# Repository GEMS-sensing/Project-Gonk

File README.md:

# Project-Gonk
Hardware files for battery holder systems with integrated protection 

## Notation
#### Example: 18650 1S3P 

18650 -> Model of battery used <br>
1S -> The number of cells in <b>series</b><br>
3P -> The number of cells in <b>parallel</b><br>

Output Voltage = SeriesNumber * CellVoltage<br>
Capacity = ParallelNumber * CellCapacity<br>

## Models
- [18650 1S3P](18650_1S3P)

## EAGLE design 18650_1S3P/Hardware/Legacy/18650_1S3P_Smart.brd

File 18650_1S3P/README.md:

# Project-Gonk 
### Battery: 18650 
### Configuration: 1S3P
Battery holder with integrated protection and control

# Usage
1. Toggle switch to "<b>OFF</b>" position
2. Verify battery voltage (Maximum difference between highest and lowest voltage cell should be less than <b>0.2V</b>)
3. Insert batteries into holders (<b>Note polarity markings</b>)
4. Verify polarity - if any of the <b>red indicator lamps</b> are lit, <b>stop!</b> Remove offending batteries and fix polarity before proceeding
5. If no red lamps are lit, connect external system to either of the <b>Vout</b> connectors (<b>observe polarity of connector!</b>)
6. Toggle switch to "<b>ON</b>" position when ready to activate 

# Repo Roadmap
#### [Documents](Documents/) 

General document and image storage for repo and README

#### [Hardware](Hardware/)

Current board files (Eagle), Bill of Materials (BoM), and other design documents

#### [Production](Production/)

Contains the various Gerber and pick and place files required to have the Printed Circuit Boards (PCBs) manufactured or populated 

## Overview
* **Type:** Power
* **Interfaces:** Power
* **Release Version:** v0.1

<!--  -->

<!--  -->

## Features
### On-Board
* Power switch
* Reverse battery indication
* Poly fuse per battery

### Interface

## Specifications
* **Output Current (Max Constant):** 5.25A
* **Current Per Battery (Max Constant):** 1.75A

## Jumper Settings 

**Configuration Jumpers**
| Jumper | Purpose | Open | Closed | Default | 
| ------ | ------- | ---------- | ---------- | ----- | 
| `JP1` | Bypass poly fuse on battery 1 | Short Circuit Protection Enabled | Short Circuit Protection Disabled | Open |  
| `JP2` | Bypass poly fuse on battery 2 | Short Circuit Protection Enabled | Short Circuit Protection Disabled | Open |
| `JP3` | Bypass poly fuse on battery 3 | Short Circuit Protection Enabled | Short Circuit Protection Disabled | Open | 

## Known Issues/Errata

#### None!

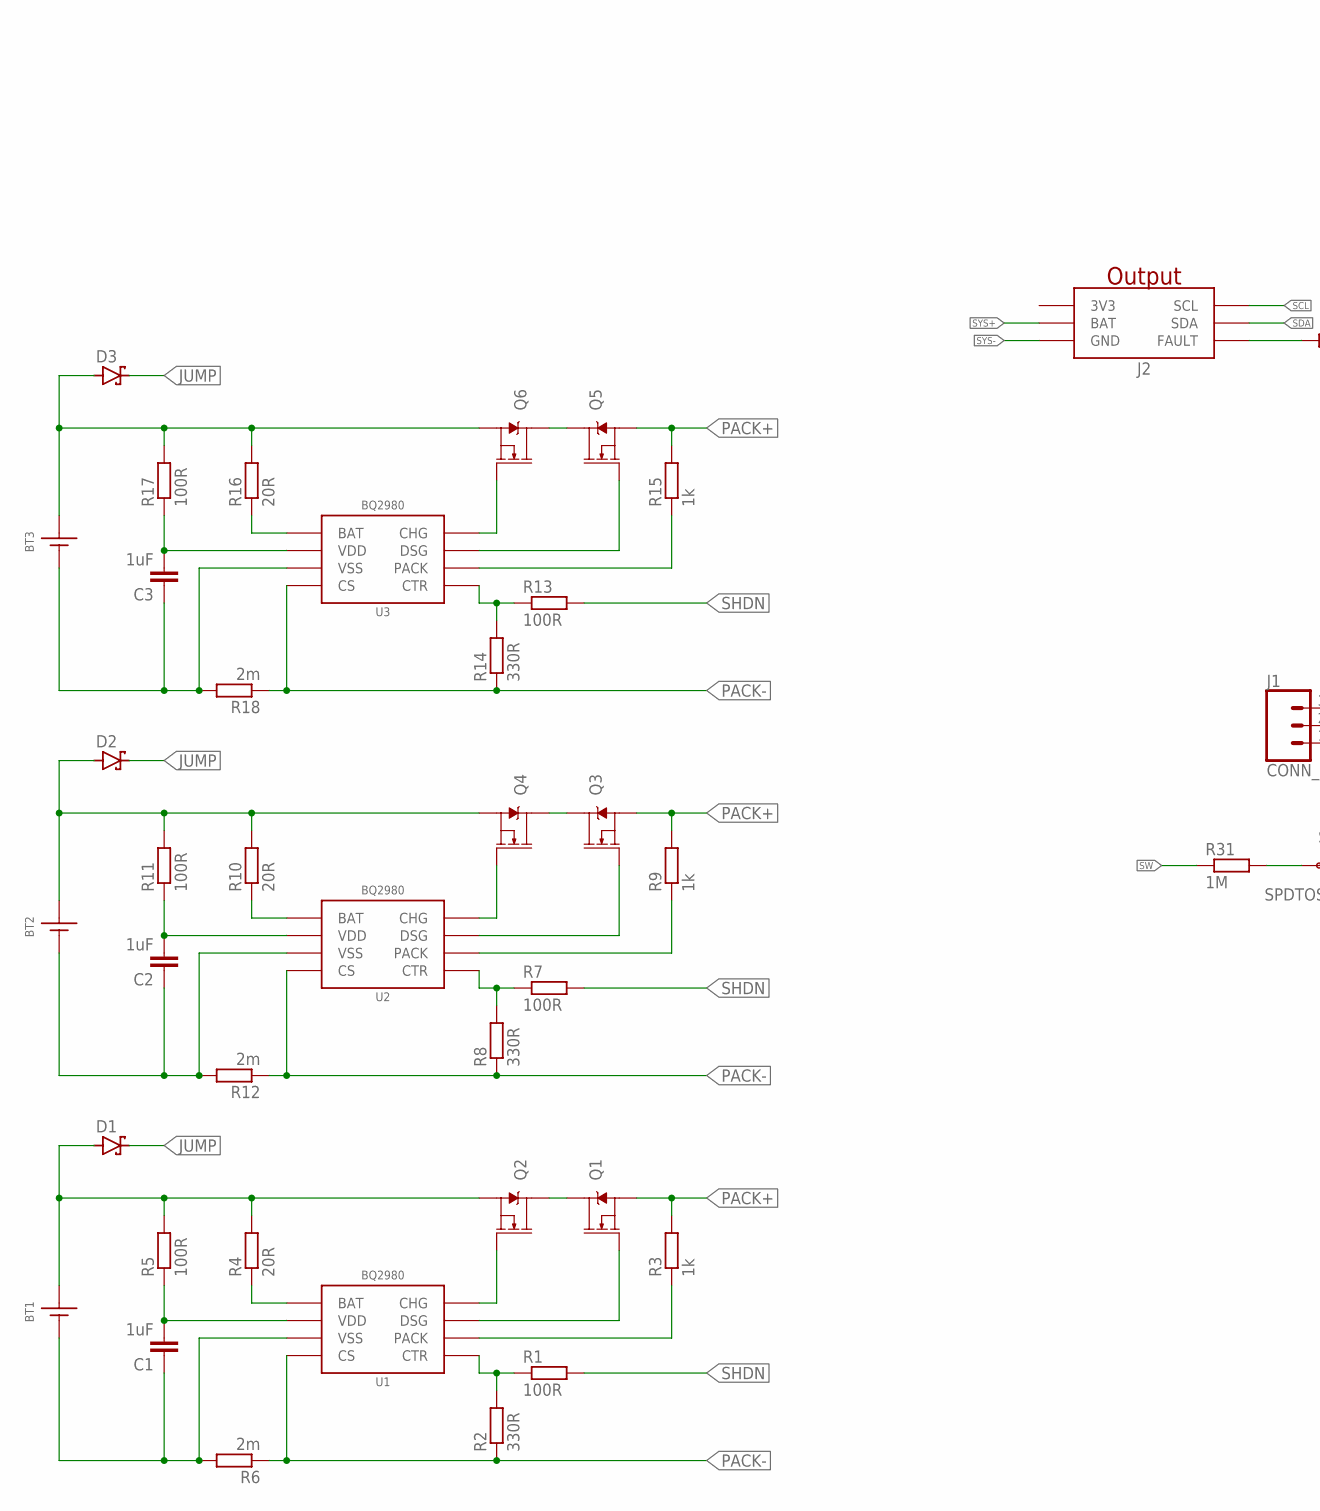
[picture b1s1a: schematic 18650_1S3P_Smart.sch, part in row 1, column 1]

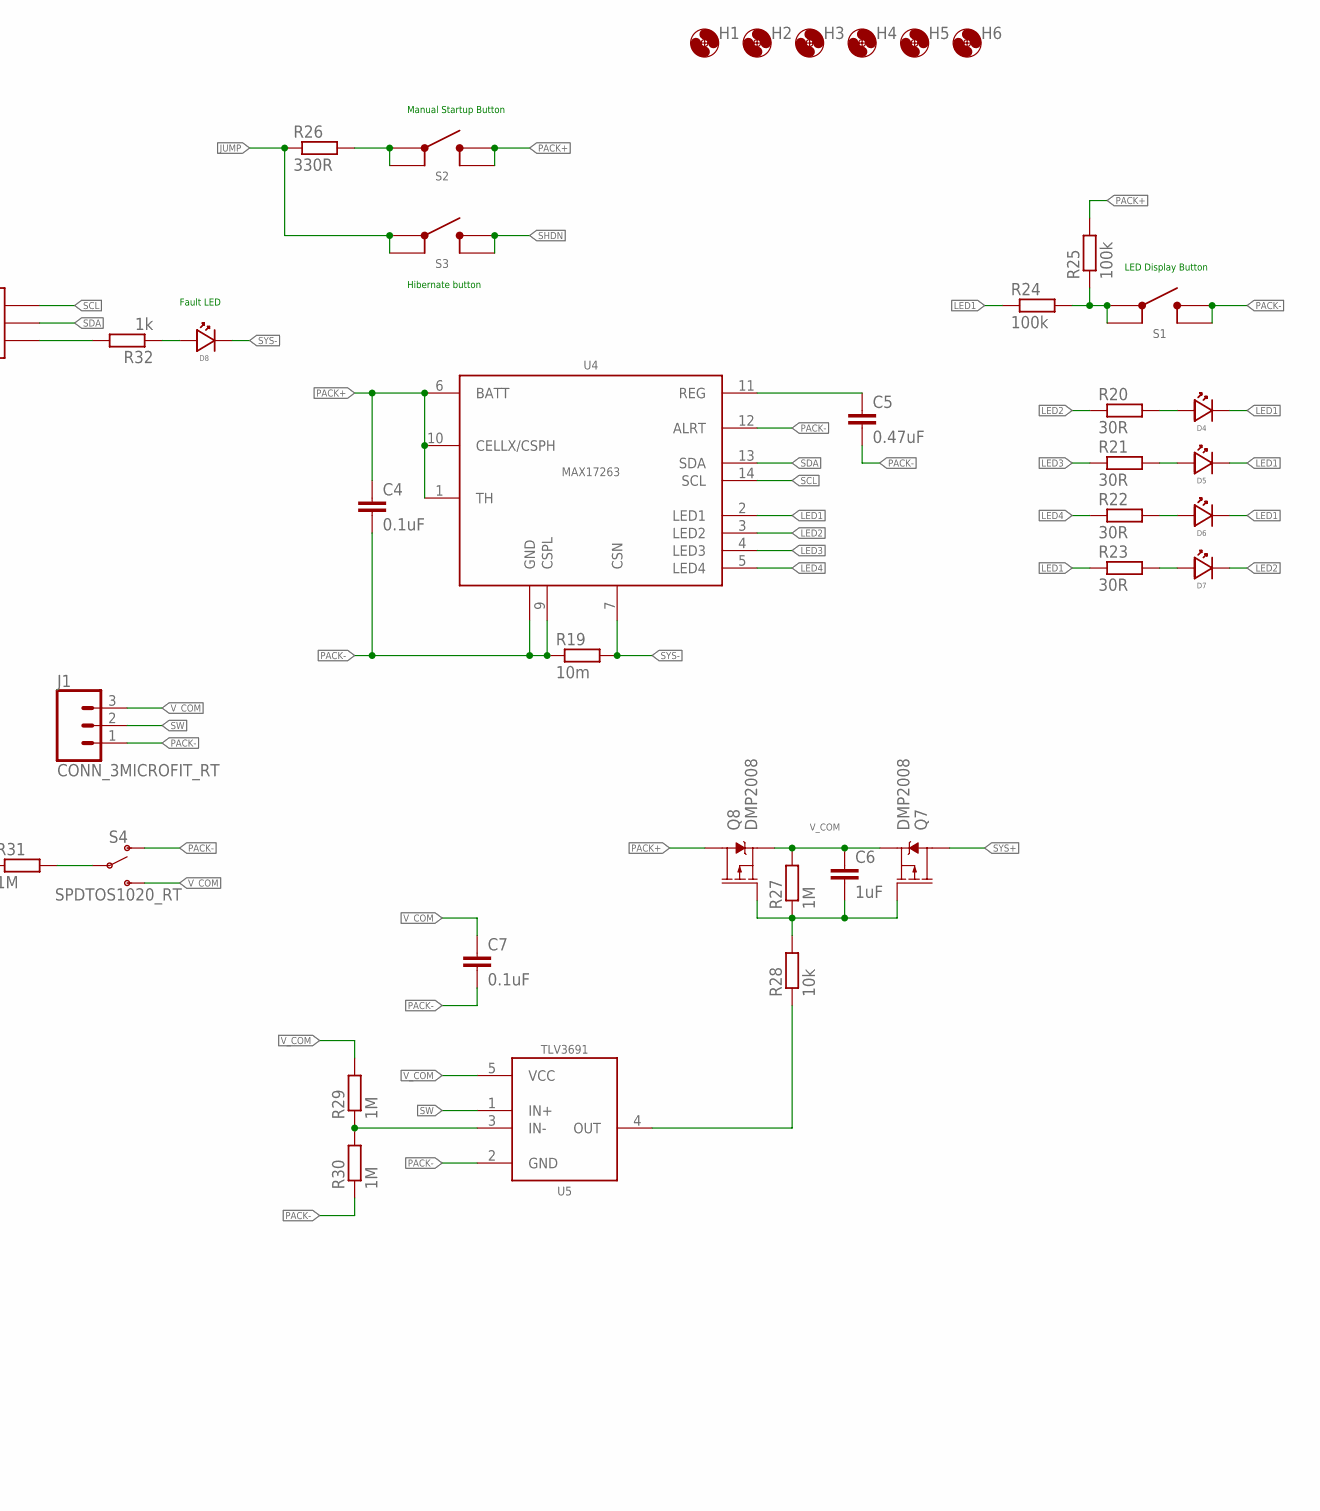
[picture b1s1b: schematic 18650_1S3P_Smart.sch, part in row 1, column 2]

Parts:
BT1, BT2, BT3: 186501042P_NOSILK; BATT_1042P_NOSILK
C1, C2, C3, C6: 1uF; C0603
C4, C7: 0.1uF; C0603
C5: 0.47uF; C0603
D1, D2, D3: DIODE_SCHOTTKYSOD-323; SOD323-R; MPN BAT54WS-7-F; DIGIKEY BAT54WS-FDICT-ND
D4, D5, D6, D7: LED1206_BOTTOM; LED_1206_BOTTOM; MPN LTST-C230KGKT; DIGIKEY 160-1456-1-ND
D8: LED1206_BOTTOM; LED_1206_BOTTOM; MPN LTST-C230KRKT; DIGIKEY 160-1457-1-ND
H1, H2, H3, H4, H5, H6: MOUNTING_HOLE4_NP; 4_40
J1: CONN_3MICROFIT_RT; 1X3_MICROFIT_RT
J2: GEMS_POWER_PLUGOUTPUT; 2X3_MICROFIT_RT
Q1, Q2, Q3, Q4, Q5, Q6: AON7522E; DFN3X3A_8L_EP1_P
Q7, Q8: DMP2008; POWERDI3333-8
R1, R5, R7, R11, R13, R17: 100R; R0603
R2, R8, R14, R26: 330R; R0603
R3, R9, R15, R32: 1k; R0603
R4, R10, R16: 20R; R0603
R6, R12, R18: 2m; R0805
R19: 10m; R0805
R20, R21, R22, R23: 30R; R0603
R24, R25: 100k; R0603
R27, R29, R30, R31: 1M; R0603
R28: 10k; R0603
S1, S2, S3: BUTTON6X6_TH; SWITCH_6MM_TH
S4: SPDTOS1020_RT; OS102011MA1QN1
U1, U2, U3: BQ2980RUG; RUG_S-PQFP-N8
U4: MAX17263; DFN_14_3X3
U5: TLV3691DCK; DCK_R-PDSO-G5

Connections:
3V3: J2.5 (3V3)
JUMP: D1.C, D2.C, D3.C, R26.1, S3.1, S3.2
LED1: D4.CATHODE, D5.CATHODE, D6.CATHODE, R23.1, R24.1, U4.2 (LED1)
LED2: D7.CATHODE, R20.1, U4.3 (LED2)
LED3: R21.1, U4.4 (LED3)
LED4: R22.1, U4.5 (LED4)
unnamed: Q1.D, Q2.D
unnamed: Q2.G, U1.8 (CHG)
unnamed: Q1.G, U1.7 (DSG)
unnamed: R1.1, R2.2, U1.5 (CTR)
unnamed: R3.1, U1.6 (PACK)
unnamed: BT1.BATT+ (+), D1.A, Q2.S@1 (S), Q2.S@2 (S), Q2.S@3 (S), R4.2, R5.2
unnamed: C1.2, R5.1, U1.2 (VDD)
unnamed: R4.1, U1.1 (BAT)
unnamed: BT1.BATT- (-), C1.1, R6.2, U1.3 (VSS)
unnamed: Q3.D, Q4.D
unnamed: Q4.G, U2.8 (CHG)
unnamed: Q3.G, U2.7 (DSG)
unnamed: R9.1, U2.6 (PACK)
unnamed: R7.1, R8.2, U2.5 (CTR)
unnamed: BT2.BATT+ (+), D2.A, Q4.S@1 (S), Q4.S@2 (S), Q4.S@3 (S), R10.2, R11.2
unnamed: C2.2, R11.1, U2.2 (VDD)
unnamed: R10.1, U2.1 (BAT)
unnamed: BT2.BATT- (-), C2.1, R12.2, U2.3 (VSS)
unnamed: Q5.D, Q6.D
unnamed: Q6.G, U3.8 (CHG)
unnamed: Q5.G, U3.7 (DSG)
unnamed: R15.1, U3.6 (PACK)
unnamed: R13.1, R14.2, U3.5 (CTR)
unnamed: BT3.BATT+ (+), D3.A, Q6.S@1 (S), Q6.S@2 (S), Q6.S@3 (S), R16.2, R17.2
unnamed: C3.2, R17.1, U3.2 (VDD)
unnamed: R16.1, U3.1 (BAT)
unnamed: BT3.BATT- (-), C3.1, R18.2, U3.3 (VSS)
unnamed: D4.ANODE, R20.2
unnamed: D5.ANODE, R21.2
unnamed: D6.ANODE, R22.2
unnamed: D7.ANODE, R23.2
unnamed: R24.2, R25.1, S1.1, S1.2
unnamed: C5.1, U4.11 (REG)
unnamed: R26.2, S2.1, S2.2
unnamed: R31.2, S4.2
unnamed: C6.2, Q7.4 (G), Q8.4 (G), R27.1, R28.2
unnamed: R28.1, U5.4 (OUT)
unnamed: J2.1 (FAULT), R32.2
unnamed: R29.1, R30.2, U5.3 (IN-)
unnamed: D8.ANODE, R32.1
PACK+: C4.1, Q1.S@1 (S), Q1.S@2 (S), Q1.S@3 (S), Q3.S@1 (S), Q3.S@2 (S), Q3.S@3 (S), Q5.S@1 (S), Q5.S@2 (S), Q5.S@3 (S), Q8.EP@1 (D), Q8.EP@2 (D), Q8.EP@3 (D), Q8.EP@4 (D), Q8.EP@5 (D), R3.2, R9.2, R15.2, R25.2, S2.3, S2.4, U4.1 (TH), U4.6 (BATT), U4.10 (CELLX/CSPH)
PACK-: C4.2, C5.2, C7.2, J1.1, R2.1, R6.1, R8.1, R12.1, R14.1, R18.1, R19.1, R30.1, S1.3, S1.4, S4.1 (O), U1.4 (CS), U2.4 (CS), U3.4 (CS), U4.8 (GND), U4.9 (CSPL), U4.12 (ALRT), U4.EP (GND), U5.2 (GND)
SCL: J2.4 (SCL), U4.14 (SCL)
SDA: J2.6 (SDA), U4.13 (SDA)
SHDN: R1.2, R7.2, R13.2, S3.3, S3.4
SW: J1.2, R31.1, U5.1 (IN+)
SYS+: J2.3 (BAT), Q7.EP@1 (D), Q7.EP@2 (D), Q7.EP@3 (D), Q7.EP@4 (D), Q7.EP@5 (D)
SYS-: D8.CATHODE, J2.2 (GND), R19.2, U4.7 (CSN)
V_COM: C6.1, C7.1, J1.3, Q7.1 (S), Q7.2 (S), Q7.3 (S), Q8.1 (S), Q8.2 (S), Q8.3 (S), R27.2, R29.2, S4.3 (S), U5.5 (VCC)

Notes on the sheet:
LED Display Button
Manual Startup Button
Hibernate button
Fault LED

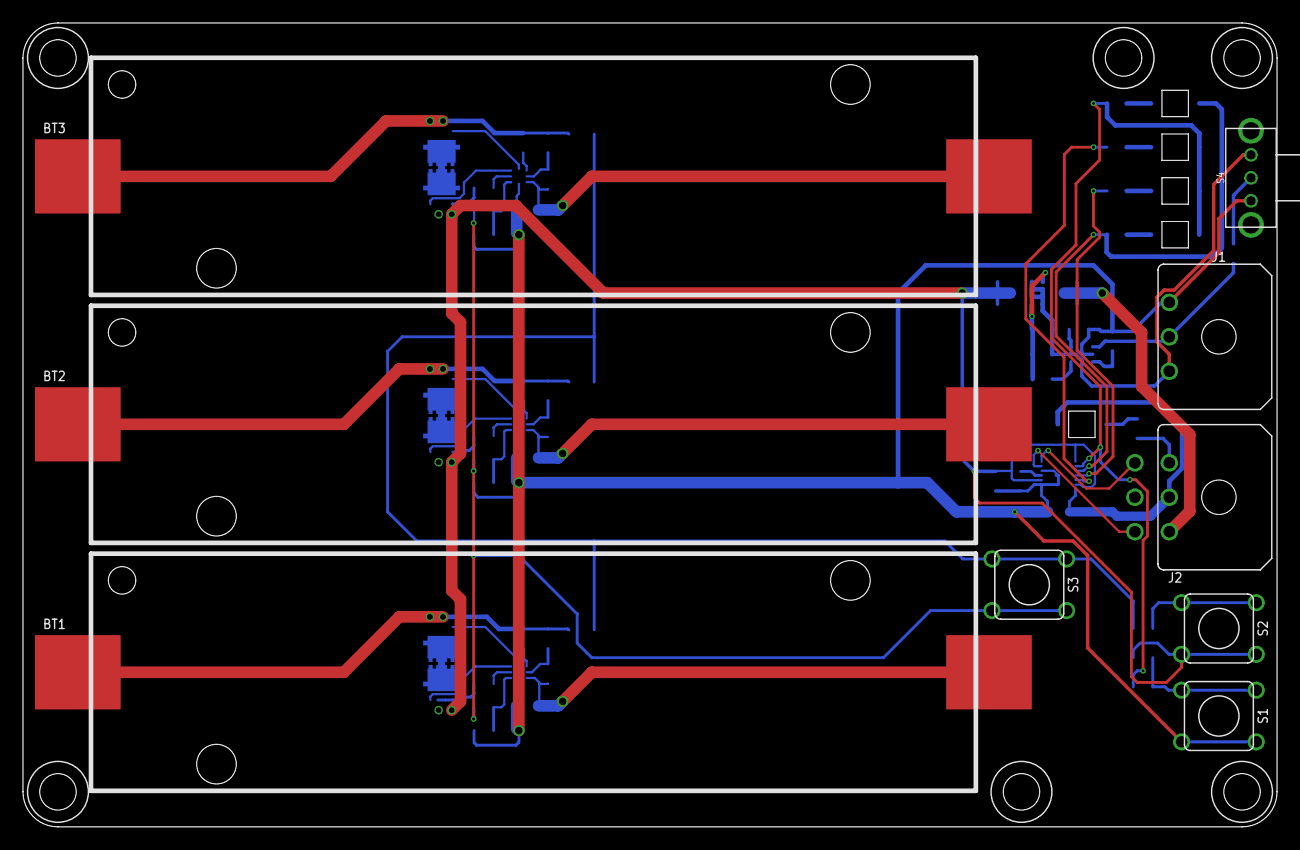
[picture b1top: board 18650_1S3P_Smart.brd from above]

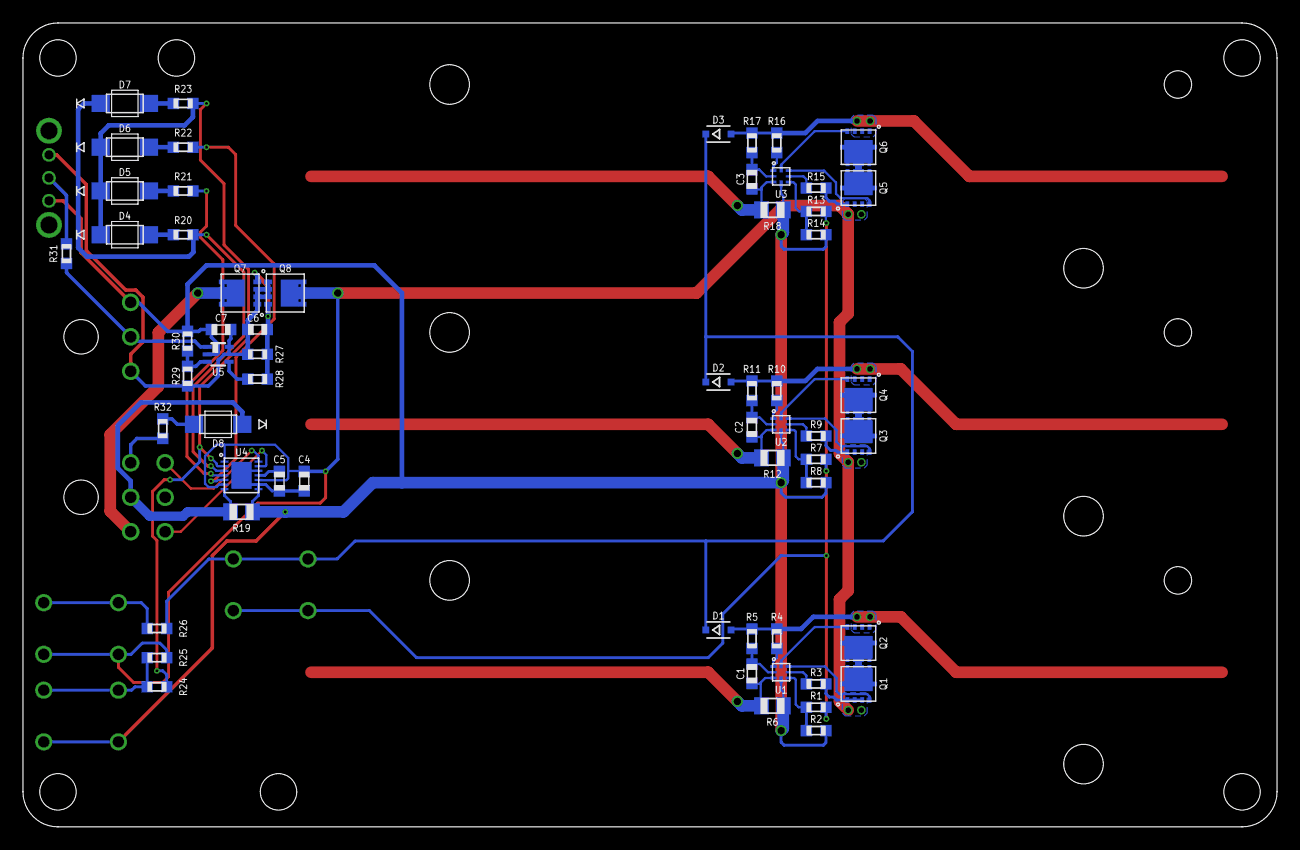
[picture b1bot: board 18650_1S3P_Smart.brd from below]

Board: 2 copper layers, 109.2 x 70.0 mm, 75 parts (60 on the bottom side), 54 nets.

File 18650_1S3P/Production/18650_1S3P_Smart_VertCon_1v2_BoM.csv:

"Qty","Value","Device","Package","Parts","Description","DIGIKEY","MF","MOUSER","MPN","VALUE","VALUE_PART",
"3","","DIODE_SCHOTTKYSOD-323","SOD323-R","D1, D2, D3","Generic Shottky Diode","BAT54WS-FDICT-ND","Diodes Inc","","BAT54WS-7-F","","",
"6","","MOUNTING_HOLE4_NP","4_40","H1, H2, H3, H4, H5, H6","Genaric Mechanical Mounting Hole","DNP","N/A","","DNP","","",
"2","0.1uF","C-EU0.1UFC0603","C0603","C4, C7","CAPACITOR, European symbol","490-6051-1-ND","Murata","","GCM188R71E104KA57D","","",
"1","0.47uF","C-EU0.47UFC0603","C0603","C5","CAPACITOR, European symbol","1276-2083-1-ND","Samsung","","CL10B474KA8NNNC","","",
"6","100R","R-EU_100R0603","R0603","R1, R5, R7, R11, R13, R17","RESISTOR, European symbol","311-100HRCT-ND","Yageo","","RC0603FR-07100RL","","100",
"2","100k","R-EU_100KR0603","R0603","R24, R25","RESISTOR, European symbol","311-100KHRCT-ND","Yageo","","RC0603FR-07100KL","","100k",
"1","10k","R-EU_10KR0603","R0603","R28","RESISTOR, European symbol","311-10.0KHRCT-ND","Yageo","","RC0603FR-0710KL","","10k",
"1","10m","R-EU_0.01R0805","R0805","R19","RESISTOR, European symbol","CRF0805-FZ-R010ELFCT-ND","Bourns","","CRF0805-FZ-R010ELF","","",
"3","186501042P_NOSILK","186501042P_NOSILK","BATT_1042P_NOSILK","BT1, BT2, BT3","Battery Holder 18650 form factor  Variant for with or without circuit protection (length varries depending on this)","36-1042P-ND","Keystone","","1042P","","",
"4","1M","R-EU_1MR0603","R0603","R27, R29, R30, R31","RESISTOR, European symbol","P1.00MHCT-ND","Panasonic","","ERJ-3EKF1004V","","1M",
"4","1k","R-EU_1KR0603","R0603","R3, R9, R15, R32","RESISTOR, European symbol","311-1KLDCT-ND","Yageo","","AC0603FR-071KL","","1k",
"4","1uF","C-EU1UFC0603","C0603","C1, C2, C3, C6","CAPACITOR, European symbol","587-1251-1-ND","Yaiyo Yuden","","EMK107BJ105KA-T","","",
"3","20R","R-EU_20R0603","R0603","R4, R10, R16","RESISTOR, European symbol","311-20.0HRCT-ND","Yageo","","RC0603FR-0720RL","","20",
"3","2m","R-EU_0.002R0805","R0805","R6, R12, R18","RESISTOR, European symbol","RHM.002AJCT-ND","Rohm","","PMR10EZPFV2L00","","",
"4","30R","R-EU_30R0603","R0603","R20, R21, R22, R23","RESISTOR, European symbol","311-30.0HRCT-ND","Yageo","","RC0603FR-0730RL","","30",
"4","330R","R-EU_330R0603","R0603","R2, R8, R14, R26","RESISTOR, European symbol","311-330HRCT-ND","Yageo","","RC0603FR-07330RL","","330",
"6","AON7522E","MOSFET-NCH-AON7522E","DFN3X3A_8L_EP1_P","Q1, Q2, Q3, Q4, Q5, Q6","N-channel MOSFET","785-1505-1-ND","Alpha & Omega","","AON7522E","AON7522E","",
"3","BQ2980RUG","BQ2980RUG","RUG_S-PQFP-N8","U1, U2, U3","BQ2980 - Voltage, Current, Temperature Protectors with an Integrated High-Side NFET (BMS)","296-47578-1-ND","TI","595-BQ298000RUGT","BQ298000RUGT","","",
"3","BUTTON6X6_TH","BUTTON6X6_TH","SWITCH_6MM_TH","S1, S2, S3","Genaric SPST Push button","450-1650-ND","TE Connectivity","","1825910-6","","",
"1","CONN_3MICROFIT_RT","CONN_3MICROFIT_RT","1X3_MICROFIT_RT","J1","Genaric 3 terminal header","WM1861-ND","Molex","","0436500300","","",
"2","DMP2008","MOSFET-PCH-DMP2008","POWERDI3333-8","Q7, Q8","P-channel MOSFET","DMP2008UFG-7DICT-ND","Diodes Inc","","DMP2008UFG-7","DMP2008","",
"1","GEMS_POWER_PLUGOUTPUT","GEMS_POWER_PLUGOUTPUT","2X3_MICROFIT","J2","Power Plug For GEMS Based SystemsBoth Input and Output versions","WM4039-ND","Molex","","0430450624","","",
"4","LED1206_BOTTOM","LED1206_BOTTOM","LED_1206_BOTTOM","D4, D5, D6, D7","Genaric LED","160-1456-1-ND","Lite-On","","LTST-C230KGKT","","",
"1","LED1206_BOTTOM","LED1206_BOTTOM","LED_1206_BOTTOM","D8","Genaric LED","160-1457-1-ND","Lite-On","","LTST-C230KRKT","","",
"1","MAX17263","MAX17263","DFN_14_3X3","U4","MAX17263 - Single/Multi-Cell Fuel Gauge with Integrated LED Control","175-MAX17263LETD+TCT-ND","Maxim","","MAX17263LETD+T","","",
"1","SPDTOS1020_RT","SPDTOS1020_RT","OS102011MA1QN1","S4","Genaric SPDT switch","CKN9559-ND","C&K","","OS102011MA1QN1","","",
"1","TLV3691DCK","TLV3691DCK","DCK_R-PDSO-G5","U5","TLV3691 - Nanopower Analog Comparator","296-37910-1-ND","TI","","TLV3691IDCKR","","",

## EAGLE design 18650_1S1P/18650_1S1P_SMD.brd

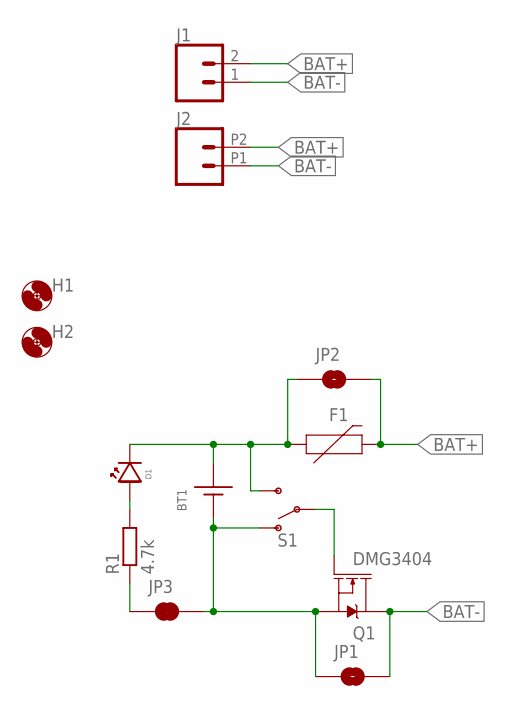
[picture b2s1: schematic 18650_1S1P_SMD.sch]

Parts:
BT1: 186501042P; BATT_1042P
D1: LED0603; LED_0603
F1: PPTC1.75A1210; 1210_BOURNS
H1, H2: MOUNTING_HOLE4_NP; 4_40
J1: CONN_023.5MM_ROUND_RESTRICT; SCREWTERMINAL-3.5MM-2_ROUND_RESTRICT
J2: CONN_022.54_SCREW_ROUND; 1X02_2.54_SCREWTERM_ROUND
JP1, JP2: JUMPER-SMT_2_NO_SILK; SMT-JUMPER_2_NO_SILK
JP3: JUMPER-SMT_2_NC_TRACE_SILK; SMT-JUMPER_2_NC_TRACE_SILK
Q1: DMG3404; SOT23-3
R1: 4.7k; R0603
S1: SPDTOS1020; OS102011MS2QN1

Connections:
BAT+: F1.2, J1.2, J2.P2 (2), JP2.2
BAT-: J1.1, J2.P1 (1), JP1.2, Q1.3 (D)
unnamed: BT1.BATT+ (+), D1.CATHODE, F1.1, JP2.1, S1.3 (S)
unnamed: D1.ANODE, R1.2
unnamed: Q1.1 (G), S1.2
unnamed: BT1.BATT- (-), JP1.1, JP3.2, Q1.2 (S), S1.1 (O)
unnamed: JP3.1, R1.1

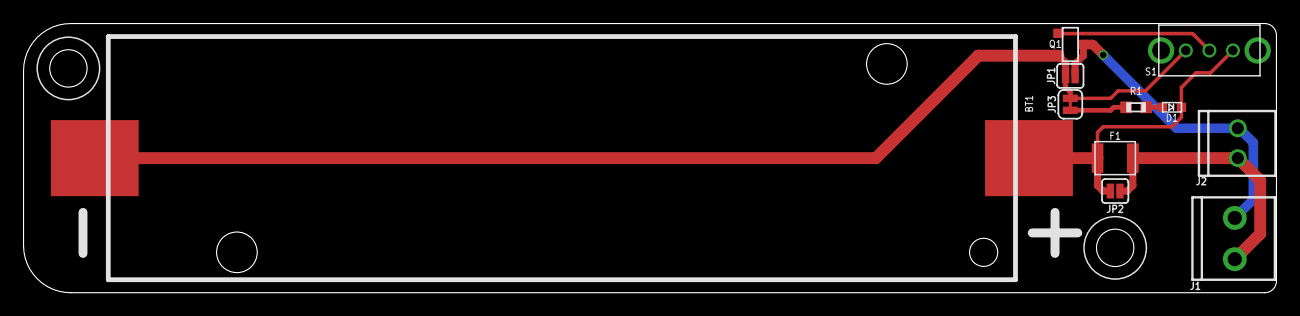
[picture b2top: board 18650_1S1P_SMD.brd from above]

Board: 2 copper layers, 106.4 x 22.9 mm, 13 parts (0 on the bottom side), 7 nets.

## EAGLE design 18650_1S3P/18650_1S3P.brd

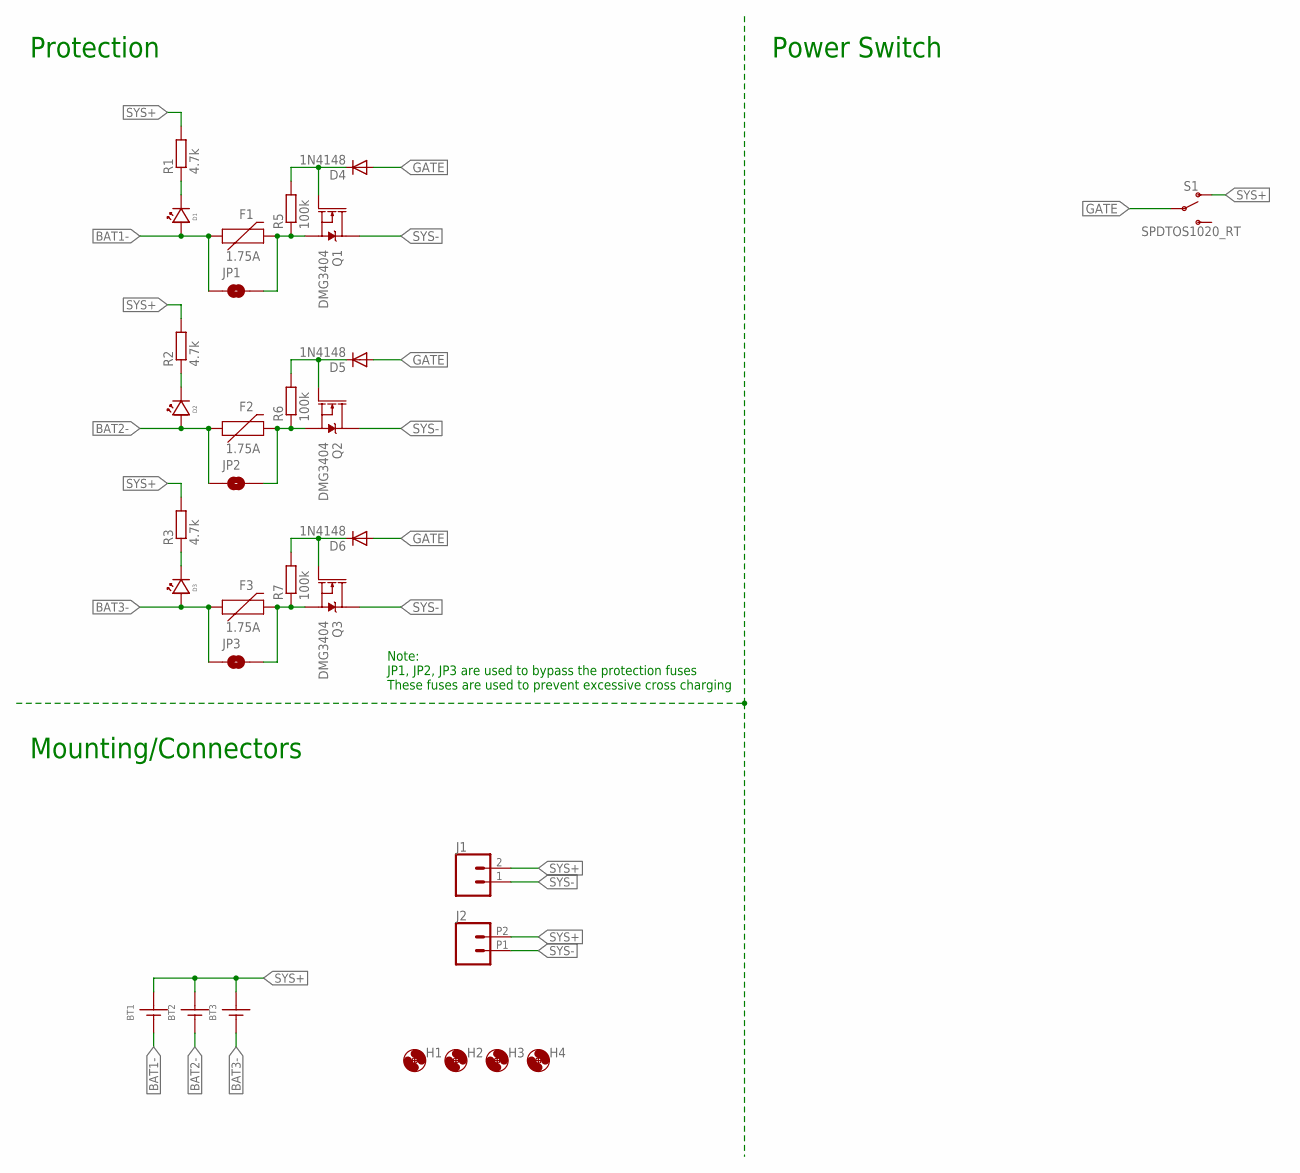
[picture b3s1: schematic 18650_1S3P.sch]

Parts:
BT1, BT2, BT3: 18650NO_PROTEC; BATT_18650_CLIP
D1, D2, D3: LED0805; LED_0805; MPN LS R976-NR-1; DIGIKEY 475-1278-1-ND
D4, D5, D6: 1N4148; SOD323-R; MPN 1N4148WS-7-F; DIGIKEY 1N4148WS-FDICT-ND
F1, F2, F3: 1.75A; 1210_BOURNS
H1, H2, H3, H4: MOUNTING_HOLE4_NP; 4_40
J1: CONN_023.5MM_ROUND_RESTRICT; SCREWTERMINAL-3.5MM-2_ROUND_RESTRICT
J2: CONN_022.54_SCREW_ROUND; 1X02_2.54_SCREWTERM_ROUND
JP1, JP2, JP3: JUMPER-SMT_2_NO_SILK; SMT-JUMPER_2_NO_SILK
Q1, Q2, Q3: DMG3404; SOT23-3
R1, R2, R3: 4.7k; R0603
R5, R6, R7: 100k; R0603
S1: SPDTOS1020_RT; OS102011MA1QN1

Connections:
BAT1-: BT1.BATT-@1 (-), BT1.BATT-@2 (-), BT1.BATT-@3 (-), D1.ANODE, F1.1, JP1.1
BAT2-: BT2.BATT-@1 (-), BT2.BATT-@2 (-), BT2.BATT-@3 (-), D2.ANODE, F2.1, JP2.1
BAT3-: BT3.BATT-@1 (-), BT3.BATT-@2 (-), BT3.BATT-@3 (-), D3.ANODE, F3.1, JP3.1
GATE: D4.A, D5.A, D6.A, S1.2
unnamed: D2.CATHODE, R2.1
unnamed: D1.CATHODE, R1.1
unnamed: F1.2, JP1.2, Q1.2 (S), R5.1
unnamed: F2.2, JP2.2, Q2.2 (S), R6.1
unnamed: D3.CATHODE, R3.1
unnamed: F3.2, JP3.2, Q3.2 (S), R7.1
unnamed: D5.C, Q2.1 (G), R6.2
unnamed: D4.C, Q1.1 (G), R5.2
unnamed: D6.C, Q3.1 (G), R7.2
SYS+: BT1.BATT+@1 (+), BT1.BATT+@2 (+), BT1.BATT+@3 (+), BT2.BATT+@1 (+), BT2.BATT+@2 (+), BT2.BATT+@3 (+), BT3.BATT+@1 (+), BT3.BATT+@2 (+), BT3.BATT+@3 (+), J1.2, J2.P2 (2), R1.2, R2.2, R3.2, S1.1 (O)
SYS-: J1.1, J2.P1 (1), Q1.3 (D), Q2.3 (D), Q3.3 (D)

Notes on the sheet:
Mounting/Connectors
Protection
Note: JP1, JP2, JP3 are used to bypass the protection fuses These fuses are used to prevent excessive cross charging
Power Switch

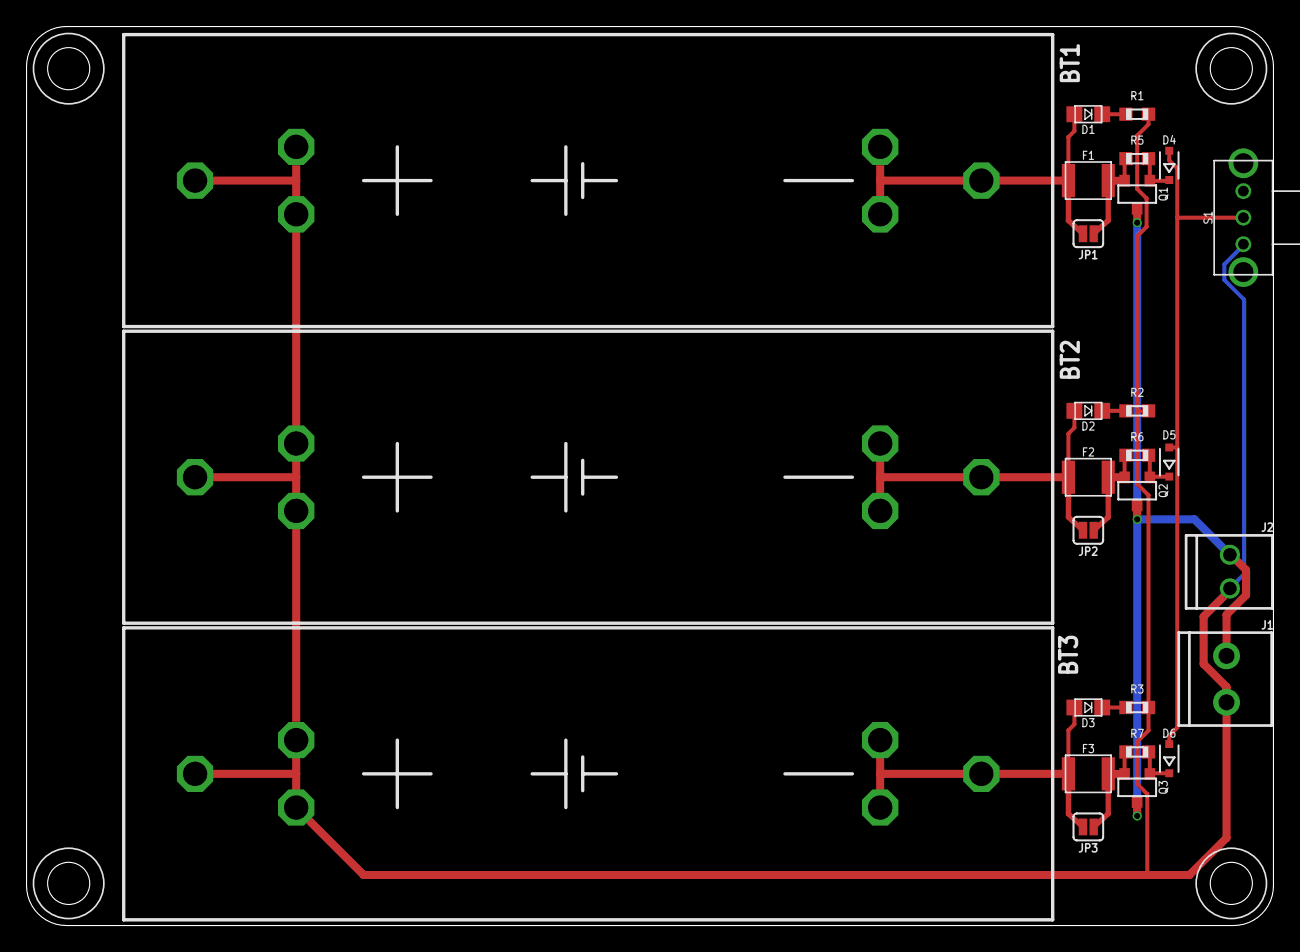
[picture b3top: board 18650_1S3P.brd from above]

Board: 2 copper layers, 94.0 x 67.7 mm, 31 parts (0 on the bottom side), 15 nets.

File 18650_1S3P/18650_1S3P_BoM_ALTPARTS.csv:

Qty,Value,Device,Package,Parts,Description,DIGIKEY,MF,MPN,VALUE,VALUE_PART
1,,CONN_022.54_SCREW_ROUND,1X02_2.54_SCREWTERM_ROUND,J2,Genaric 2 terminal header,ED10561-ND,OnShore,OSTVN02A150,,
1,,CONN_023.5MM_ROUND_RESTRICT,SCREWTERMINAL-3.5MM-2_ROUND_RESTRICT,J1,Genaric 2 terminal header,ED2635-ND,On Shore,OSTTE020161,,
4,,MOUNTING_HOLE4_NP,4_40,"H1, H2, H3, H4",Genaric Mechanical Mounting Hole,DNP,N/A,DNP,,
3,1.75A,PPTC1.75A1210,1210_BOURNS,"F1, F2, F3",Bel Fuse PPTC,MF-USMF175X-2CT-ND,Bourns,MF-USMF175X-2,,
3,100k,R-EU_100KR0603,R0603,"R5, R6, R7","RESISTOR, European symbol",311-100KHRCT-ND,Yageo,RC0603FR-07100KL,,100k
3,18650NO_PROTEC,18650NO_PROTEC,BATT_18650_CLIP,"BT1, BT2, BT3",Battery Holder 18650 form factor  Variant for with or without circuit protection (length varries depending on this),36-54-ND,Keystone,54,,
3,BAS16WX,DIODESOD-323,SOD323-R,"D4, D5, D6",Genaric Diode,BAS16WXTPMSDKR-ND,Micro Semi,BAS16WX-TP,,
3,4.7k,R-EU_4.7KR0603,R0603,"R1, R2, R3","RESISTOR, European symbol",311-4.70KHRCT-ND,Yageo,RC0603FR-074K7L,,4.7k
3,DMG3406,MOSFET-NCH-DMG3406L,SOT23-3,"Q1, Q2, Q3",N-channel MOSFETs,DMG3406L-13DICT-ND,Diodes Incorporated,DMG3406L-13,DMG3406,
3,JUMPER-SMT_2_NO_SILK,JUMPER-SMT_2_NO_SILK,SMT-JUMPER_2_NO_SILK,"JP1, JP2, JP3",Normally open jumper,N/A,N/A,DNP,,
3,LED0805,LED0805,LED_0805,"D1, D2, D3",Genaric LED,1497-XZMDK54W-4DKR-ND,SunLED,XZMDK54W-4,,
1,SPDTOS1020_RT,SPDTOS1020_RT,OS102011MA1QN1,S1,Genaric SPDT switch,CKN9559-ND,C&K,OS102011MA1QN1,,

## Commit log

2020-05-06 Initial v0.0 system
    Late stage push of the v0.0 system, updates coming after testing of prototype hardware
2020-05-07 Update for v0.1 system
    Updated system to v0.1, changed switching and reverse polarity protection system, ready for fab
2020-05-07 Added readme and changed file structure
    Added readme with use instructions for the v0.1 18650 1S3P holder as well as general readme
2020-07-01 Updated diode part number, new BoM
    Fixed diode part number to be correct SOD323 diode instead of SOD523 diode, regenerated BoM to reflect change
2020-07-01 Added DNP to mount holes
2020-12-15 Added additional markdown docs, changed folder structure
    Added more markdown docs, changed how the folders are structured to at least emulate the standard being used by the GEMS system
2020-12-15 Added images
2020-12-16 Adjusted image
2020-12-21 Added 1S1P 18650 boards
    Added SMD and PTH versions of a 1S1P breakout boards for 18650s
2020-12-21 Added external switch designs
    Added designs for an external switch to control a future battery board, gerbers sent to fab
2021-02-20 1S3P - Smart schematic capture, very preliminary layout
    Input schematic and began rough layout process for 1S3P smart board
2021-02-23 Continued layout of 1S3P Smart
    Continued layout, connections made, labeling and cleanup required. Made fix to `ALERT` pin connection (had connected to `GND` erroneously vs `PACK-`)
2021-02-23 Layout and ref designator cleanup, ready for final verification
    Continued layout cleanup, layout should be final barring final verification
2022-03-09 Backlog v0.0 and v0.1 updates
2022-03-09 Added 18650_1S3P_Smart v1.0
2022-03-09 Added 18650_1S3P_Smart v1.1
2022-03-09 Added 18650_1S3P_Smart v1.2 (very and normal)
    Added v1.2 updates for both systems
2022-03-09 Updated to use non-polarized battery holder
2022-03-30 Create LICENSE
2022-12-15 Changed folder structure to include legacy aspects
    Also changed 1042P to 1042 to match manufactured version

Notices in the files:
parts and their libraries:
bschulz: This work is licensed under the Creative Commons Attribution-ShareAlike 4.0
http://creativecommons.org/licenses/by-sa/4.0
SparkFun-Jumpers: Licensing: Creative Commons ShareAlike 4.0 International - https://creativecommons.org/licenses/by-sa/4.0
